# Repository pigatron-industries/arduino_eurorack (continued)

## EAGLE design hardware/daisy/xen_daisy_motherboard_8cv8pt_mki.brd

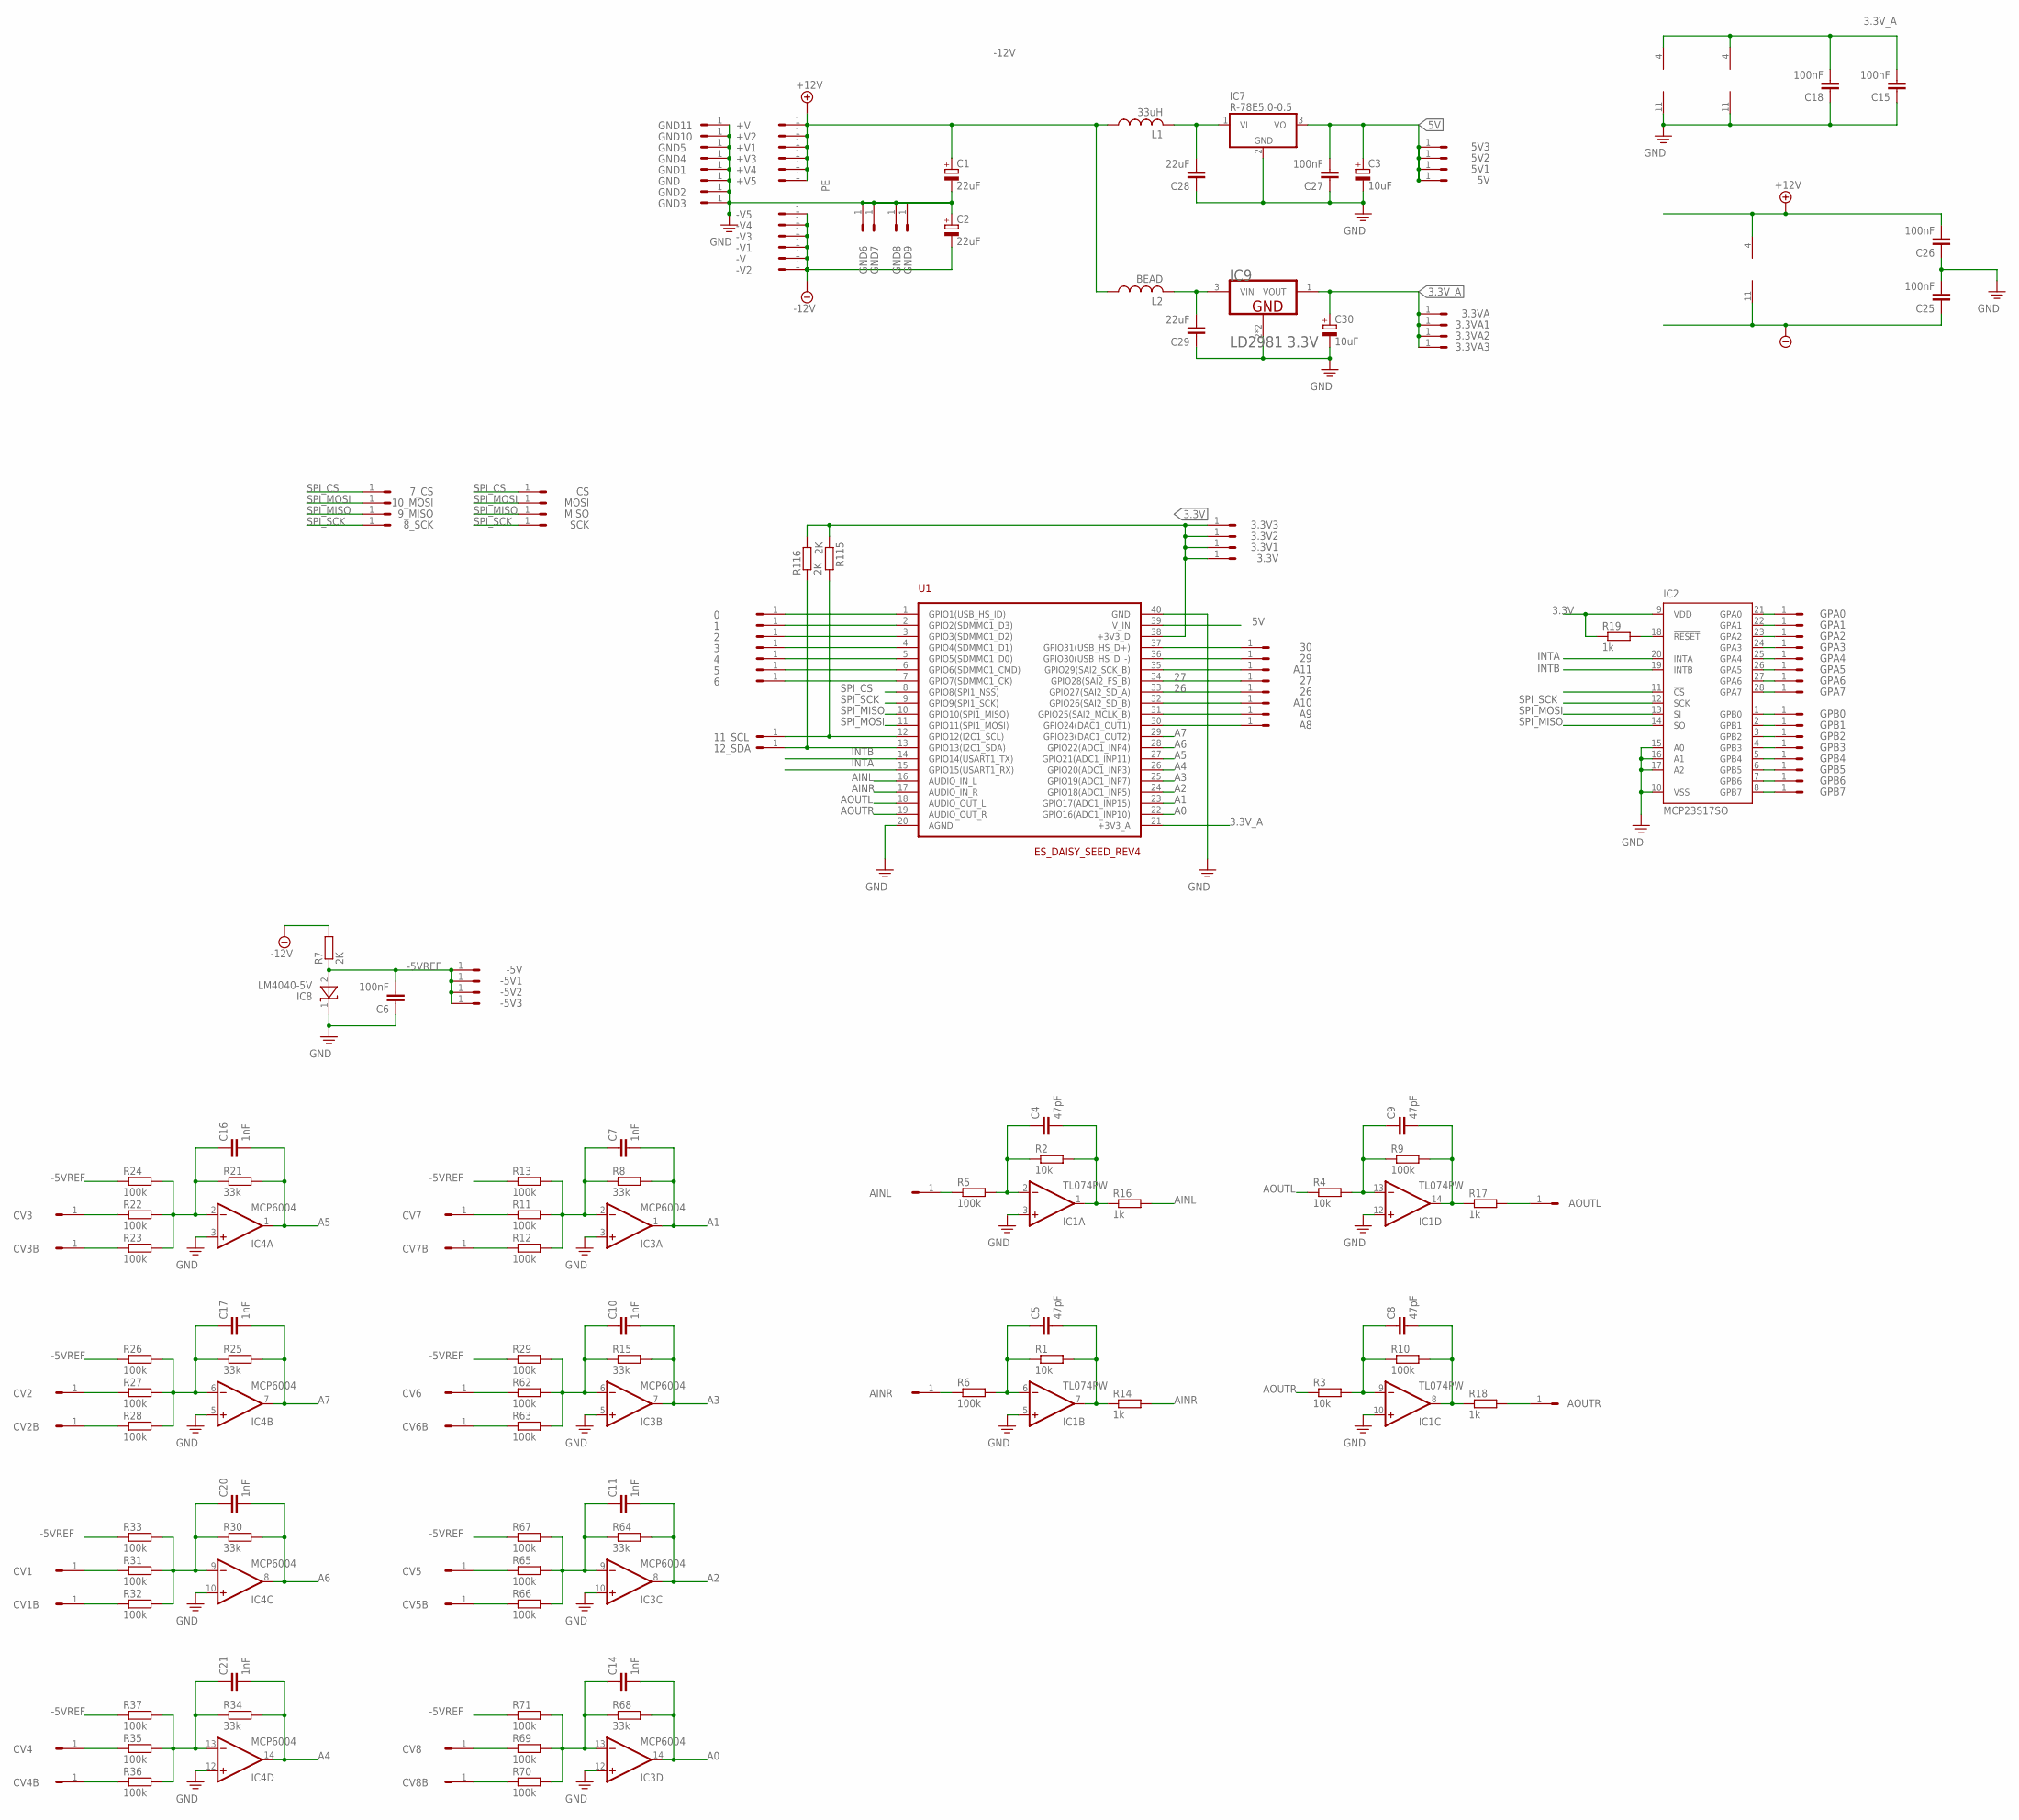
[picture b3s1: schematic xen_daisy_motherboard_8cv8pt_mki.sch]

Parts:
0, 1, 2, 3, 3.3V, 3.3V1, 3.3V2, 3.3V3, 3.3VA, 3.3VA1, 3.3VA2, 3.3VA3, 4, 5, 5V, 5V1, 5V2, 5V3, 6, 7_CS, 8_SCK, 9_MISO, 10_MOSI, 11_SCL, 12_SDA, 26, 27, 29, 30: HEADER/MALE/01
+V, +V1, +V2, +V3, +V4, +V5: HEADER/MALE/01
-5V, -5V1, -5V2, -5V3: HEADER/MALE/01
-V, -V1, -V2, -V3, -V4, -V5: HEADER/MALE/01
A8, A9, A10, A11: HEADER/MALE/01
AINL: HEADER/MALE/01
AINR: HEADER/MALE/01
AOUTL: HEADER/MALE/01
AOUTR: HEADER/MALE/01
C1, C2: 22uF; SV-C
C3, C30: 10uF; SV-B
C4, C5, C8, C9: 47pF; C0603
C6, C15, C18, C25, C26, C27: 100nF; C0603
C7, C10, C11, C14, C16, C17, C20, C21: 1nF; C0603
C28, C29: 22uF; C0805
CS: HEADER/MALE/01
CV1, CV1B, CV2, CV2B, CV3, CV3B, CV4, CV4B, CV5, CV5B, CV6, CV6B, CV7, CV7B, CV8, CV8B: HEADER/MALE/01
GND, GND1, GND2, GND3, GND4, GND5, GND6, GND7, GND8, GND9, GND10, GND11: HEADER/MALE/01
GPA0, GPA1, GPA2, GPA3, GPA4, GPA5, GPA6, GPA7: HEADER/MALE/01
GPB0, GPB1, GPB2, GPB3, GPB4, GPB5, GPB6, GPB7: HEADER/MALE/01
IC1: TL074PW; TSSOP14
IC2: MCP23S17SO; SO28W
IC3, IC4: MCP6004; TSSOP14
IC7: R-78E5.0-0.5; WE78
IC8: LM4040-5V; SOT-23
IC9: LD2981 3.3V; LD2981-SOT89
L1: 33uH; L2012C
L2: BEAD; R0603
MISO: HEADER/MALE/01
MOSI: HEADER/MALE/01
R1, R2, R3, R4: 10k; R0603
R5, R6, R9, R10, R11, R12, R13, R22, R23, R24, R26, R27, R28, R29, R31, R32, R33, R35, R36, R37, R62, R63, R65, R66, R67, R69, R70, R71: 100k; R0603
R7, R115, R116: 2K; R0603
R8, R15, R21, R25, R30, R34, R64, R68: 33k; R0603
R14, R16, R17, R18, R19: 1k; R0603
SCK: HEADER/MALE/01
U1: ES_DAISY_SEED_REV4; ES_DAISY_SEED

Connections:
3.3V: 3.3V.1, 3.3V1.1, 3.3V2.1, 3.3V3.1, IC2.9 (VDD), R19.1, R115.1, R116.2, U1.38 (+3V3_D)
3.3V_A: 3.3VA.1, 3.3VA1.1, 3.3VA2.1, 3.3VA3.1, C15.2, C18.2, C30.+, IC3.4 (V+), IC4.4 (V+), IC9.1 (VOUT), U1.21 (+3V3_A)
5V: 5V.1, 5V1.1, 5V2.1, 5V3.1, C3.+, C27.2, IC7.3 (VO), U1.39 (V_IN)
26: 26.1, U1.33 (GPIO27(SAI2_SD_A))
27: 27.1, U1.34 (GPIO28(SAI2_FS_B))
+12V: +V.1, +V1.1, +V2.1, +V3.1, +V4.1, +V5.1, C1.+, C26.2, IC1.4 (V+), L1.1, L2.1
-5VREF: -5V.1, -5V1.1, -5V2.1, -5V3.1, C6.2, IC8.2 (A), R7.1, R13.1, R24.1, R26.1, R29.1, R33.1, R37.1, R67.1, R71.1
-12V: -V.1, -V1.1, -V2.1, -V3.1, -V4.1, -V5.1, C2.-, C25.1, IC1.11 (V-), R7.2
A0: C14.2, IC3.14 (OUT), R68.2, U1.22 (GPIO16(ADC1_INP10))
A1: C7.2, IC3.1 (OUT), R8.2, U1.23 (GPIO17(ADC1_INP15))
A2: C11.2, IC3.8 (OUT), R64.2, U1.24 (GPIO18(ADC1_INP5))
A3: C10.2, IC3.7 (OUT), R15.2, U1.25 (GPIO19(ADC1_INP7))
A4: C21.2, IC4.14 (OUT), R34.2, U1.26 (GPIO20(ADC1_INP3))
A5: C16.2, IC4.1 (OUT), R21.2, U1.27 (GPIO21(ADC1_INP11))
A6: C20.2, IC4.8 (OUT), R30.2, U1.28 (GPIO22(ADC1_INP4))
A7: C17.2, IC4.7 (OUT), R25.2, U1.29 (GPIO23(DAC1_OUT2))
AINL: R16.2, U1.16 (AUDIO_IN_L)
AINR: R14.2, U1.17 (AUDIO_IN_R)
AOUTL: R4.1, U1.18 (AUDIO_OUT_L)
AOUTR: R3.1, U1.19 (AUDIO_OUT_R)
INTA: IC2.20 (INTA), U1.15 (GPIO15(USART1_RX))
INTB: IC2.19 (INTB), U1.14 (GPIO14(USART1_TX))
unnamed: CV2.1, R27.1
unnamed: A8.1, U1.30 (GPIO24(DAC1_OUT1))
unnamed: A9.1, U1.31 (GPIO25(SAI2_MCLK_B))
unnamed: A10.1, U1.32 (GPIO26(SAI2_SD_B))
unnamed: A11.1, U1.35 (GPIO29(SAI2_SCK_B))
unnamed: C5.1, IC1.6 (-IN), R1.1, R6.2
unnamed: C4.1, IC1.2 (-IN), R2.1, R5.2
unnamed: C7.1, IC3.2 (-IN), R8.1, R11.2, R12.2, R13.2
unnamed: C4.2, IC1.1 (OUT), R2.2, R16.1
unnamed: C5.2, IC1.7 (OUT), R1.2, R14.1
unnamed: AOUTL.1, R17.2
unnamed: AOUTR.1, R18.2
unnamed: CV7B.1, R12.1
unnamed: CV7.1, R11.1
unnamed: C9.1, IC1.13 (-IN), R4.2, R9.1
unnamed: C10.1, IC3.6 (-IN), R15.1, R29.2, R62.2, R63.2
unnamed: C8.1, IC1.9 (-IN), R3.2, R10.1
unnamed: CV6.1, R62.1
unnamed: CV6B.1, R63.1
unnamed: AINL.1, R5.1
unnamed: C8.2, IC1.8 (OUT), R10.2, R18.1
unnamed: CV3.1, R22.1
unnamed: C9.2, IC1.14 (OUT), R9.2, R17.1
unnamed: C16.1, IC4.2 (-IN), R21.1, R22.2, R23.2, R24.2
unnamed: AINR.1, R6.1
unnamed: CV2B.1, R28.1
unnamed: CV3B.1, R23.1
unnamed: 29.1, U1.36 (GPIO30(USB_HS_D_-))
unnamed: C17.1, IC4.6 (-IN), R25.1, R26.2, R27.2, R28.2
unnamed: C21.1, IC4.13 (-IN), R34.1, R35.2, R36.2, R37.2
unnamed: CV4.1, R35.1
unnamed: CV4B.1, R36.1
unnamed: 30.1, U1.37 (GPIO31(USB_HS_D+))
unnamed: CV1B.1, R32.1
unnamed: CV1.1, R31.1
unnamed: C20.1, IC4.9 (-IN), R30.1, R31.2, R32.2, R33.2
unnamed: 0.1, U1.1 (GPIO1(USB_HS_ID))
unnamed: 1.1, U1.2 (GPIO2(SDMMC1_D3))
unnamed: 2.1, U1.3 (GPIO3(SDMMC1_D2))
unnamed: 3.1, U1.4 (GPIO4(SDMMC1_D1))
unnamed: 11_SCL.1, R115.2, U1.12 (GPIO12(I2C1_SCL))
unnamed: 4.1, U1.5 (GPIO5(SDMMC1_D0))
unnamed: 5.1, U1.6 (GPIO6(SDMMC1_CMD))
unnamed: 6.1, U1.7 (GPIO7(SDMMC1_CK))
unnamed: IC2.18 (!RESET), R19.2
unnamed: C28.2, IC7.1 (VI), L1.2
unnamed: 12_SDA.1, R116.1, U1.13 (GPIO13(I2C1_SDA))
unnamed: GPB7.1, IC2.8 (GPB7)
unnamed: GPB6.1, IC2.7 (GPB6)
unnamed: GPB5.1, IC2.6 (GPB5)
unnamed: C14.1, IC3.13 (-IN), R68.1, R69.2, R70.2, R71.2
unnamed: GPB4.1, IC2.5 (GPB4)
unnamed: GPB3.1, IC2.4 (GPB3)
unnamed: CV8.1, R69.1
unnamed: GPB2.1, IC2.3 (GPB2)
unnamed: GPB1.1, IC2.2 (GPB1)
unnamed: GPB0.1, IC2.1 (GPB0)
unnamed: GPA7.1, IC2.28 (GPA7)
unnamed: GPA6.1, IC2.27 (GPA6)
unnamed: GPA5.1, IC2.26 (GPA5)
unnamed: GPA4.1, IC2.25 (GPA4)
unnamed: CV8B.1, R70.1
unnamed: CV5B.1, R66.1
unnamed: CV5.1, R65.1
unnamed: C11.1, IC3.9 (-IN), R64.1, R65.2, R66.2, R67.2
unnamed: C29.2, IC9.3 (VIN), L2.2
unnamed: GPA3.1, IC2.24 (GPA3)
unnamed: GPA2.1, IC2.23 (GPA2)
unnamed: GPA1.1, IC2.22 (GPA1)
unnamed: GPA0.1, IC2.21 (GPA0)
PE: C1.-, C2.+, C3.-, C6.1, C15.1, C18.1, C25.2, C26.1, C27.1, C28.1, C29.1, C30.-, GND.1, GND1.1, GND2.1, GND3.1, GND4.1, GND5.1, GND6.1, GND7.1, GND8.1, GND9.1, GND10.1, GND11.1, IC1.3 (+IN), IC1.5 (+IN), IC1.10 (+IN), IC1.12 (+IN), IC2.10 (VSS), IC2.15 (A0), IC2.16 (A1), IC2.17 (A2), IC3.3 (+IN), IC3.5 (+IN), IC3.10 (+IN), IC3.11 (V-), IC3.12 (+IN), IC4.3 (+IN), IC4.5 (+IN), IC4.10 (+IN), IC4.11 (V-), IC4.12 (+IN), IC7.2 (GND), IC8.1 (C), IC9.2 (GND), IC9.2-2 (GND), U1.20 (AGND), U1.40 (GND)
SPI_CS: 7_CS.1, CS.1, U1.8 (GPIO8(SPI1_NSS))
SPI_MISO: 9_MISO.1, IC2.14 (SO), MISO.1, U1.10 (GPIO10(SPI1_MISO))
SPI_MOSI: 10_MOSI.1, IC2.13 (SI), MOSI.1, U1.11 (GPIO11(SPI1_MOSI))
SPI_SCK: 8_SCK.1, IC2.12 (SCK), SCK.1, U1.9 (GPIO9(SPI1_SCK))

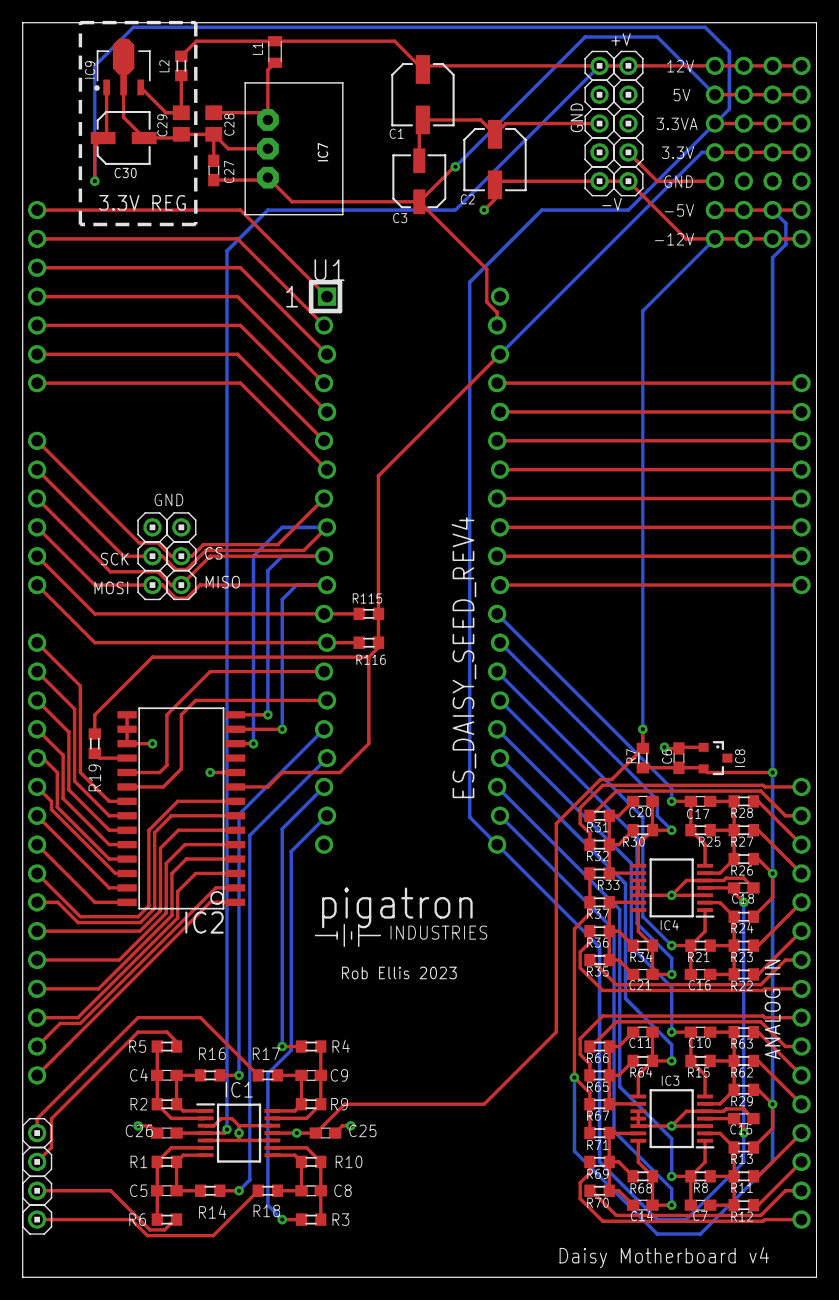
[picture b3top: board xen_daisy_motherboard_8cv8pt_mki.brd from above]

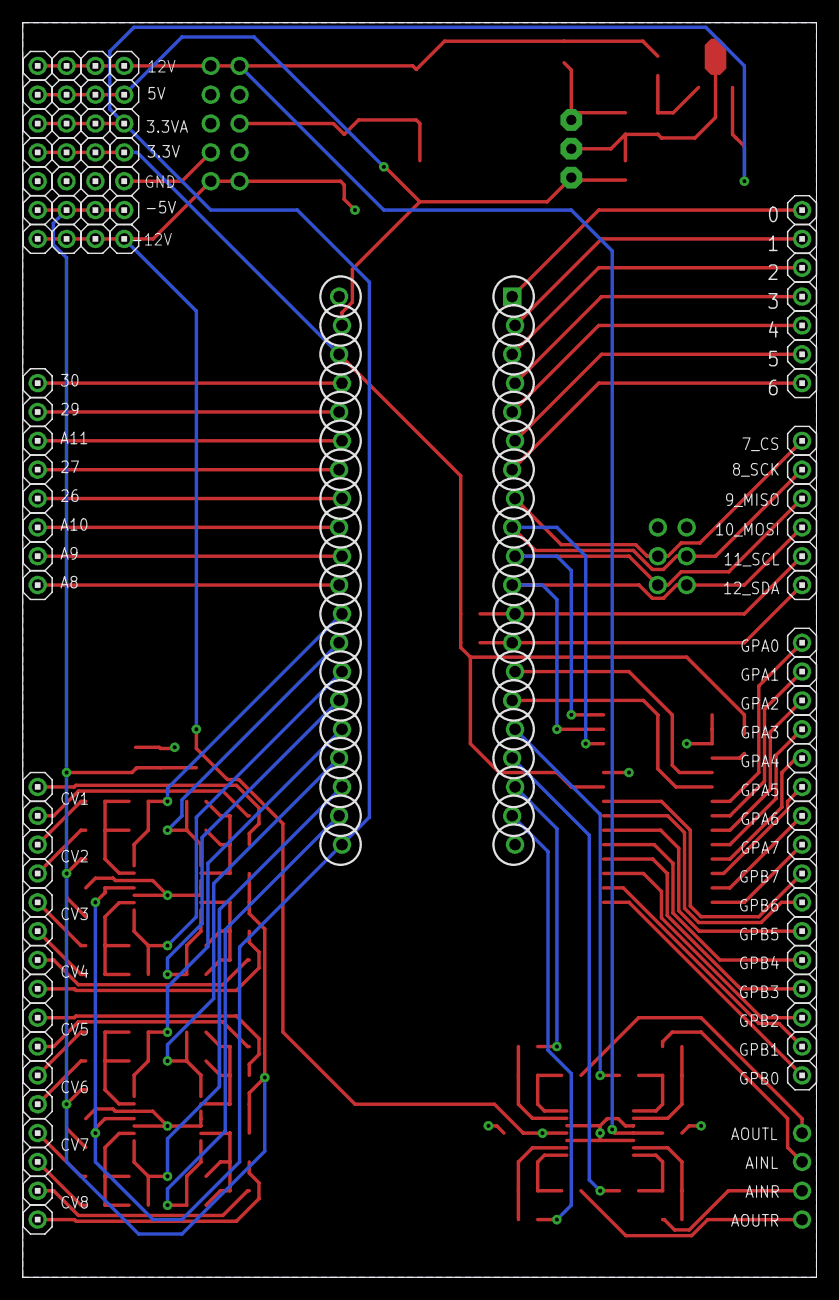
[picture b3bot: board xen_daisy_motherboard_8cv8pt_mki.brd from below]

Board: 2 copper layers, 69.9 x 110.5 mm, 184 parts (81 on the bottom side), 97 nets.

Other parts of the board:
U$1: PIGATRON-LOGO

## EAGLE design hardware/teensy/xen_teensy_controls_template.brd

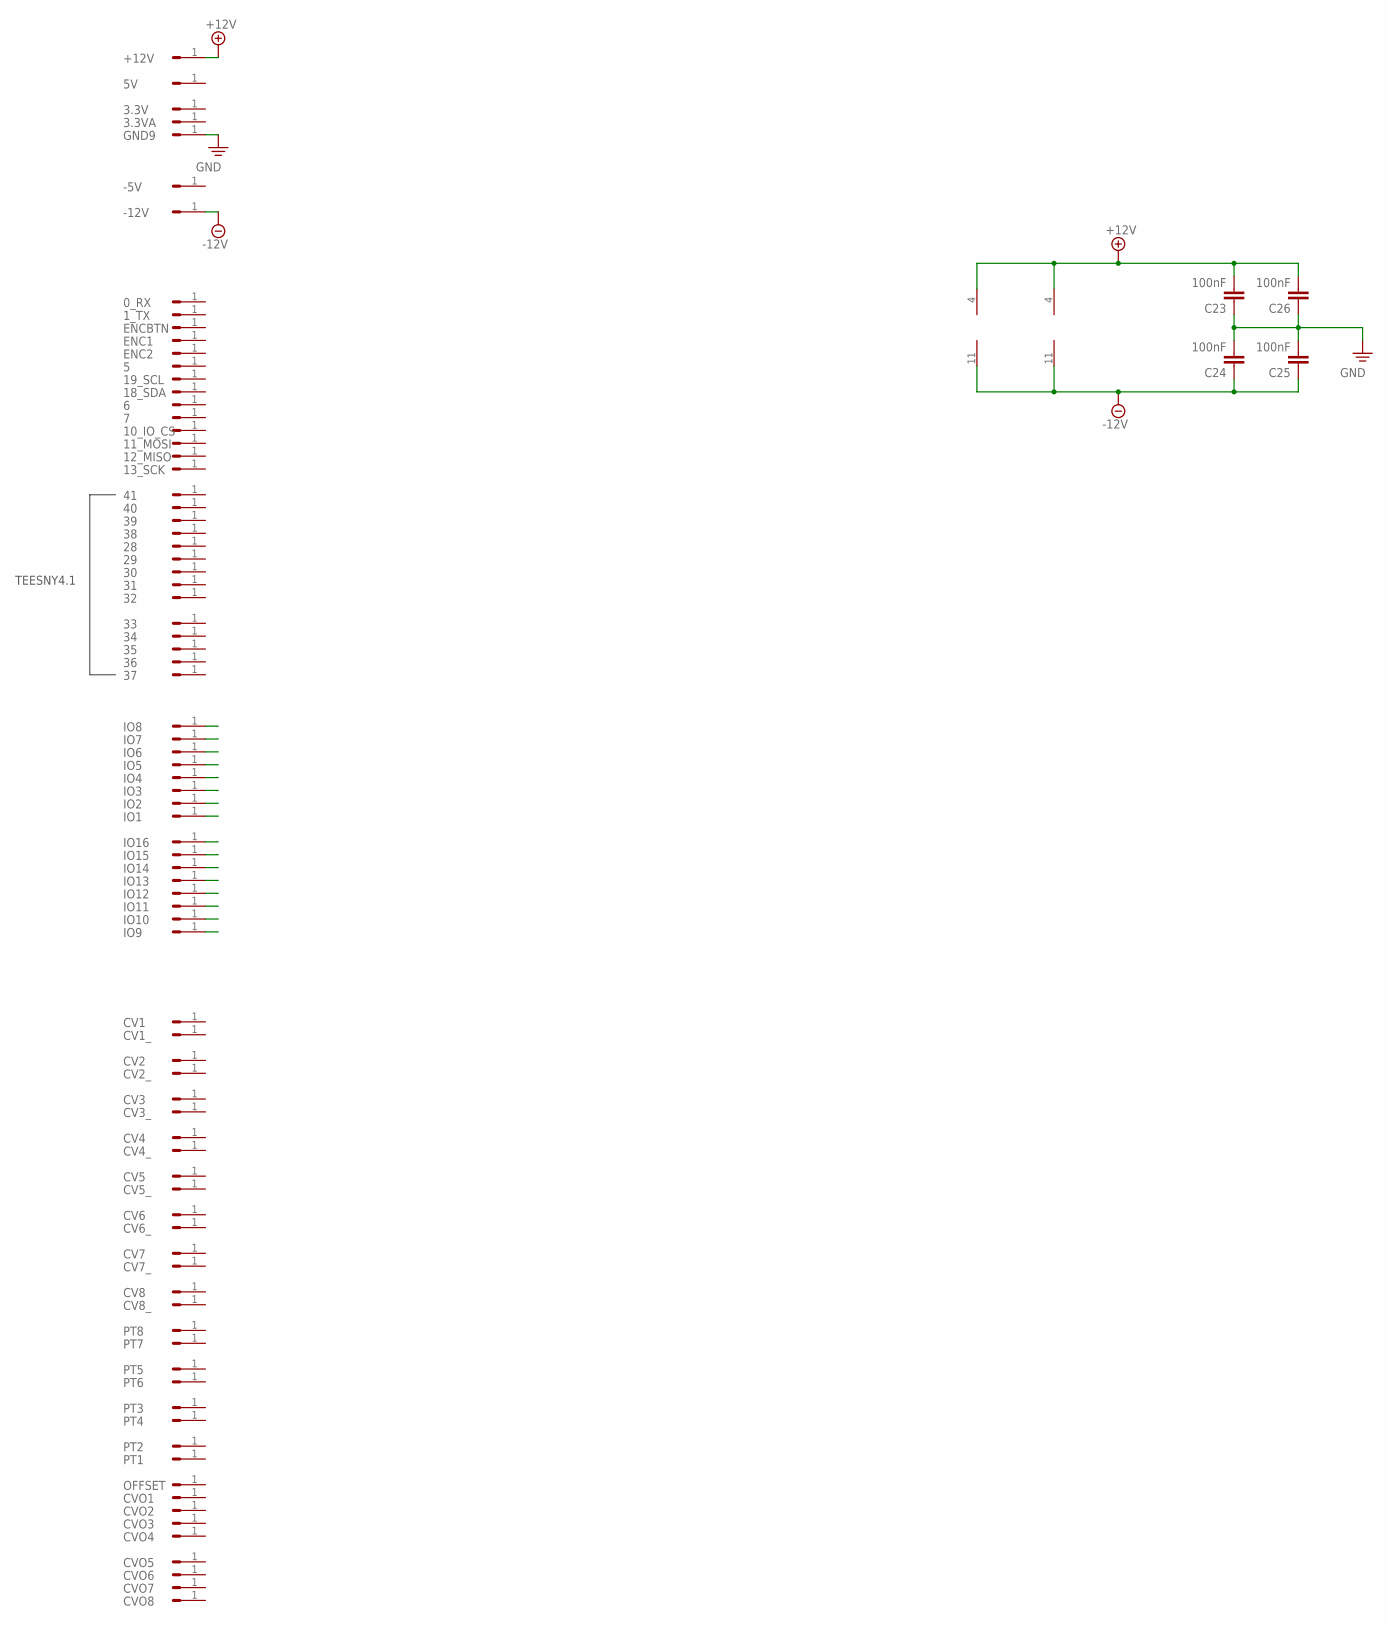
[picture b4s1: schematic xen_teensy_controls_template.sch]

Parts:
0_RX, 1_TX, 3.3V, 3.3VA, 5, 5V, 6, 7, 10_IO_CS, 11_MOSI, 12_MISO, 13_SCK, 18_SDA, 19_SCL, 28, 29, 30, 31, 32, 33, 34, 35, 36, 37, 38, 39, 40, 41: HEADER/MALE/01
+12V: HEADER/MALE/01
-5V, -12V: HEADER/MALE/01
C23, C24, C25, C26: 100nF; C0603
CV1, CV1_, CV2, CV2_, CV3, CV3_, CV4, CV4_, CV5, CV5_, CV6, CV6_, CV7, CV7_, CV8, CV8_: HEADER/MALE/01
CVO1, CVO2, CVO3, CVO4, CVO5, CVO6, CVO7, CVO8: HEADER/MALE/01
ENC1, ENC2: HEADER/MALE/01
ENCBTN: HEADER/MALE/01
GND9: HEADER/MALE/01
IC1, IC5: TL074D; SO14
IO1, IO2, IO3, IO4, IO5, IO6, IO7, IO8, IO9, IO10, IO11, IO12, IO13, IO14, IO15, IO16: HEADER/MALE/01
OFFSET: HEADER/MALE/01
PT1, PT2, PT3, PT4, PT5, PT6, PT7, PT8: HEADER/MALE/01

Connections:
+12V: +12V.1, C23.2, C26.2, IC1.4 (V+), IC5.4 (V+)
-12V: -12V.1, C24.1, C25.1, IC1.11 (V-), IC5.11 (V-)
PE: C23.1, C24.2, C25.2, C26.1, GND9.1

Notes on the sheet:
TEESNY4.1

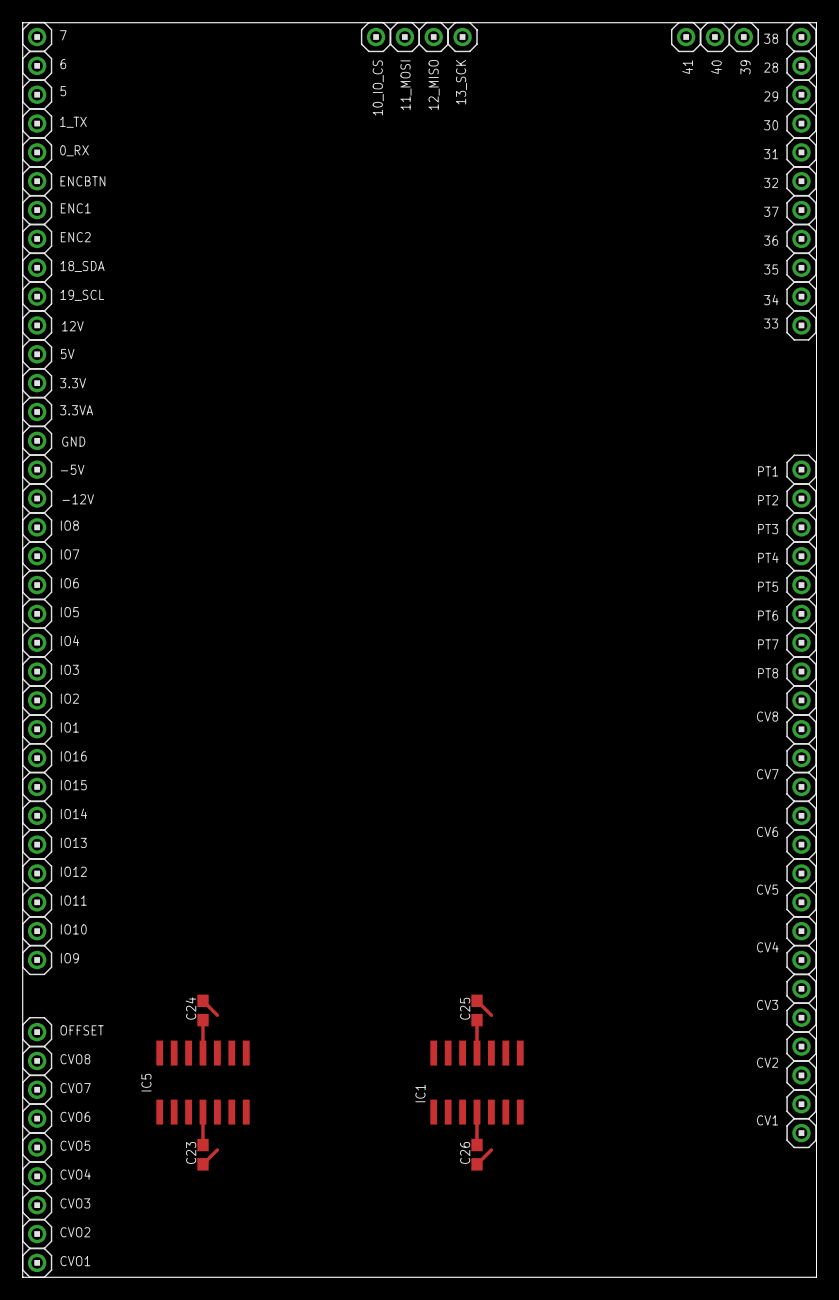
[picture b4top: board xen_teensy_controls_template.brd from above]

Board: 2 copper layers, 69.9 x 110.5 mm, 91 parts (0 on the bottom side), 3 nets.

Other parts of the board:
U$1: PIGATRON-LOGO

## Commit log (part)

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2021-09-04 Added set range methods
2021-09-04 Added compile tests and fixed issues
2021-09-04 inlined methods
2021-09-04 use references
2021-09-04 Set voltage range of max11300 pins
2021-09-04 default to NativeDevice
2021-09-04 add pullup pin type
2021-09-04 automatically set pin type
2021-09-04 auto set pin types
2021-09-04 macros for defining native io
2021-09-04 removed debounce.begin call becasue it crashes
2021-09-04 implement deferred output for max11300
2021-09-04 Fix compile error
2021-09-12 V0.2 (#2)
    * v0.2 rewrite
    * Fix hc595 error
    * Used virtual inheritance
    * Added binary read method
    * Added set range methods
    * Added compile tests and fixed issues
2021-09-12 Add getSize
2021-09-27 Add pin enable method
2021-09-28 Added IS32FL3738 led driver as analog output device
2021-10-02 Fix for range scale not working when to values are inverted
2021-10-02 DAC8164 device driver
2021-10-02 Added set duration for trigger
2021-10-02 getPhase method
2021-10-03 Add filter, move oscillator
2021-10-03 include math.h
2021-10-10 Array wrapper
2021-10-10 Array operator
2021-10-12 Sample Buffer
2021-10-12 Set sampleRate
2021-10-16 Added MemPool class and SamplePlayer
2021-10-17 Add teensy motherboard pcb
2021-10-30 decalre overloaded new operator to make this compile on teensy for now
2021-10-30 Rewritten envelope to use segments instead of points
2021-10-30 Added sustain to envelope
2021-10-30 Only return true if gate has changed
2021-11-14 const [] operator
2021-11-15 Moved hardware
2021-11-18 profiler
2021-11-18 seperate print from end
2021-11-18 fix method name
2021-11-21 Add speed to SlewLimiter constructor
2021-12-05 Correct method name
2021-12-06 Add DelayLine
2021-12-06 Made MemPool a template
2021-12-06 don't use new to allocate memory
2021-12-06 Fixed delay line position calcualtion
2021-12-06 set total delay
2021-12-20 Use template type for pointer type
2021-12-20 Added const
2021-12-20 Set max clock speed for i2c
2021-12-28 Adde AbstractMainController and Config
2021-12-28 Add clock and clock divider
2021-12-29 Fixed bugs in HC595Device
2021-12-29 Removed MultiplexGateOutput, use HC595Device instead
2021-12-29 Remove MultiplexGateOutput
2021-12-29 Add Timer include
2021-12-29 Added Wire.h
2021-12-29 made interface he same as GateOutput
2021-12-29 initialise in constructor
2022-01-02 Inverted gate input
2022-01-15 Reduce default trigger voltage to 2v
2022-01-28 Added waveshapes and WaveOscillator
2022-01-28 added waveshapes to include
2022-01-28 Made controllerInit virtual
2022-01-28 option to invert gate input
2022-01-29 Added setPhase method
2022-01-29 Allow oscillator to have negative frequency
2022-01-29 Base class for oscillators
2022-01-29 Fix local variable bug
2022-01-29 Set length of each segment to equal 1
2022-01-29 Added AsymmetricalTriangle
2022-01-29 calculate gradient and total length when changing line length
2022-01-29 Replace envelope with waves shape based envelope
2022-01-29 Don't do anything if gate value didn't change
2022-01-30 Replaced WaveList with WaveSelector
2022-01-30 Add ObjectSelector to include
2022-01-30 Add array operator to ObjectSelector
2022-01-30 Fix error
2022-01-31 Add cycle methods
2022-01-31 getSize method
2022-02-01 Renamed ObjectSelector
2022-02-01 Use ObjectSelector instead of ControllerList
2022-02-01 Use TypeSelector to select controllers
2022-02-01 Fixed bug setting index to 0
2022-02-02 Changed constants due to clashes with arduino framework
2022-02-04 Add AbstrctController
2022-02-04 Add AbstractController
2022-02-04 object to manage an encoder with button together
2022-02-04 use combined encoder and button in main controller
2022-02-04 Adding eurorack namespace
2022-02-04 Added eurorack namespace
2022-02-04 Removed old oscillator class
2022-02-04 Added bandlimited waveforms
2022-02-04 method to enable polyblep
2022-02-04 Set oscillator amplitude
2022-02-06 WaveTable
2022-02-06 WaaveTable
2022-02-06 Add getTableFrequency
2022-02-06 Added isInited method
2022-02-06 Add temp buffer to WaveTable
2022-02-06 Added WaveTable super class
2022-02-06 Added WaveTableFactory
2022-02-06 Added namespace
2022-02-07 Aadded missing incrementPhase()
2022-02-11 Add missing return statement
2022-02-11 WaveSelector and TypeSelector constructors
2022-02-11 WaveInterpolator
2022-02-12 Updated hardware
2022-02-12 Phase distortion oscillator
2022-02-13 Added basic 2 line distortion function
2022-02-15 Added maxPhase variable
2022-02-15 Update docs
2022-02-19 Return last value if after end of sequence
2022-02-19 Made some methods protected
2022-02-24 Split up getEncoderEvent to make it easier to override
2022-02-25 AnalogGateOutput
2022-02-26 setLength method
2022-02-27 Set theme jekyll-theme-tactile
2022-02-27 index.md
2022-02-27 formatting
2022-02-27 Documentation links
2022-02-27 -5v reference circuit
2022-02-27 added style
2022-02-27 doc theme
2022-02-27 override layout
2022-02-27 layout
2022-02-27 Link to documentation
2022-02-27 doc style
2022-02-27 Add logo
2022-02-27 move links to sidebar
2022-02-27 link to homepage
2022-02-27 Add links in sidebar
2022-02-27 links to pages
2022-02-27 fix url
2022-02-27 Ordered pages
2022-02-27 Highlight acrive page
2022-02-27 fix navigation
2022-02-28 Header font
2022-02-28 use baseUrl
2022-02-28 change title
2022-02-28 fix baseUrl
2022-02-28 baseurl
2022-02-28 try to fix baseurl
2022-02-28 add slash
2022-03-03 use css from main site
2022-03-03 use style from main site
2022-03-03 layout change
2022-03-04 no title for main page
2022-03-05 use common layout
2022-03-05 basic usage
2022-03-05 features and status
2022-03-05 nested bullets
2022-03-05 split tested and untested list
2022-03-05 moved usage to new page
2022-03-06 typo
2022-03-10 smooth step function
2022-03-10 Constructor
2022-03-10 calc coefficients in constructor
2022-03-11 Update TriggerInput to use device pins
2022-03-11 remove old TriggerInput
2022-03-11 remove old TrigggerInput
2022-03-11 Changed Object selector to Array selector
2022-03-11 Fix issue
2022-03-12 Moved interpolator logic to base class
2022-03-12 Change to private inheritance
2022-03-12 Add array operator
2022-03-12 2D and 3D Interpolators
2022-03-12 docs
2022-03-12 renamed
2022-03-12 title
2022-03-12 chnaged title levels
2022-03-12 images
2022-03-13 interpolatot docs
2022-03-13 WaveInterpolator2D
2022-03-14 Set pin types in init function
2022-03-14 Add getSize method
2022-03-14 Moved function to .h file
2022-03-15 enable interrupts on init
2022-03-16 Enable deferred output
2022-03-16 Set interrupt pin to input
2022-03-16 Receive method to read all input pins
2022-03-16 added deferred input
2022-03-17 check for digital_input_pullup
2022-03-17 deferred initialization
2022-03-18 don't read pin value in constructor
2022-03-18 Removed digital read from constructor
2022-03-18 EnumInput
2022-03-18 Enum input fix
2022-03-18 EnumInput fix
2022-03-19 teensy motherboard docs
2022-03-19 hardware docs
2022-03-19 add labels to image
2022-03-19 made image bigger
2022-03-19 add header
2022-03-19 numbering
2022-03-19 pin label
2022-03-19 labels
2022-03-19 rotate labels
2022-03-20 crop image
2022-03-20 label power
2022-03-20 pin descriptions
2022-03-20 Teensy connections
2022-03-20 resize
2022-03-21 Check index is within range
2022-03-21 don't deferr init on native device
2022-03-21 Add SDB pin
2022-03-21 Split out saveMode function
2022-03-21 remove selected reference as it was always referencing first item
2022-03-21 AnalogInputSumPin
2022-03-25 Changed templates to allow other analog pin types to be passed in
2022-03-25 add constant for default mid value
2022-03-25 change to unsigned
2022-03-27 Increase default trigger length
2022-03-27 Add pullup option to DigitalInputPin
2022-03-31 Added state varialbe to envelope
2022-04-01 Prevent envelope attack and decay jumping if gate changes when not fully finished phase
2022-04-02 renamed AbstractInput to AbstractAnalogInput
2022-04-02 Add invert parameter to DigitalInput macro
2022-04-02 Add isTriggeredOff function
2022-04-02 update AnalogGateInput doc
2022-04-02 inherit directly from AbstractAnalogInput
2022-04-02 Add debounce to analog gate input
2022-04-10 Allow to change base value
2022-04-12 Reduce noise on analog inputs by averaging and discarding outliers
2022-04-12 PowerFunction
2022-04-12 Constructor parameters
2022-04-12 AnalogInputFilter
2022-04-13 Init for NativeDevice
2022-04-13 Use ADC library for teensy
2022-04-13 Swap custom noise filtering with hardware averaging
2022-04-13 Remove custom NoiseFilter
2022-04-13 configure all adc modules
2022-04-14 Add stabilise threshold back in
2022-04-15 get state and frequency, min wait time for external clock
2022-04-16 replace EnumInput with IntegerInput
2022-04-17 use 0.49 to prevent round outside of range
2022-04-18 update template
2022-04-18 Don't let long hold events prevent rotation event from triggering.
2022-04-28 Array initialiser
2022-04-29 changed traces
2022-05-01 Change dependencies
2022-05-01 contains method
2022-05-22 Added handy operators
2022-05-23 bug fix
2022-06-08 Add ArrayPtr to allow passing arrays without knowing size at compile time
2022-06-11 Set output range
2022-06-11 Add sd card reader
2022-06-11 sd header
2022-06-11 initialise as sdio when not setting csPin
2022-06-11 common begin function
2022-06-11 add BufferFileReader to header
2022-06-11 add const
2022-06-11 simple wildcard match function
2022-06-12 moved mempool added linked list
2022-06-12 add object
2022-06-18 getObjects
2022-06-18 Allow encoder control schem to be redefined
2022-06-18 Cyle value methods
2022-06-18 extra constructors
2022-06-18 option to initialise on mode select
2022-07-02 add SdFat
2022-07-02 getObjects method
2022-07-02 Store reciprocal of length to make gradient calculation more efficient
2022-07-02 inlined
2022-07-02 set length in constructor
2022-07-09 Add calibrated scale to analog pins
2022-07-09 Add offset and scale methods
2022-07-09 recalculate factor after scale and offset
2022-07-09 load ans save analog pin calibration
2022-07-09 changed scale direction
2022-08-04 Added pin calibration class
2022-08-05 Added error on array overflow
2022-08-12 Allow second encoder
2022-08-13 added clear function and remove memory deletions
2022-08-20 Add graphics layout library
2022-08-21 Horizontal container
2022-08-21 FieldComponent minor updates
2022-09-12 documentation
2022-09-12 Try SPI, fallback to SDIO
2022-09-19 removed calls the sd.end() as it closes the spi bus completely
2022-09-20 getTrigger without resetting
2022-09-20 add save and load method to controller
2022-09-20 moved methods to abstract controller
2022-12-03 importing SPI.h avoids compile errors in projects that don't import it
2022-12-03 call save method after changing mode
2023-06-18 use unsigned char for file reader buffer
2023-06-20 memmem implementation
2023-07-14 add seperate double and single encoder controllers
2023-07-14 separate controllers for double encoder
2023-07-19 parameterized controller
2023-07-21 remove superclass
2023-08-17 remove item from array
2023-10-22 add selectValue method
2023-10-22 add heldFor duration method
2023-10-22 fix heldFor function
2023-10-29 add getPin function
2023-10-29 add get scale and offset methods
2023-11-11 fix bug with config check
2023-11-27 Allow cycle enums to be cycled and selected
2024-01-20 add init function to Array
2024-01-22 split out external clock and add tests
2024-01-26 add clock divider to external clock
2024-01-26 add test
2024-01-26 add clock multiplier
2024-01-26 if external tick is late wait for it
2024-01-26 add InternalExternalClock to include header
2024-01-26 fix include
2024-01-26 remove inline
2024-01-27 add set items and get method
2024-03-23 include LinkedList
2024-03-23 Remove ObjectManager
2024-03-23 remove mempool from LinkedList constructor, add allocateObject function
2024-03-23 remove mempool
2024-03-25 allocate buffer in generic mempool
2024-03-26 encoder non-interrupt mode
2024-03-26 make saveState virtual
2024-03-27 filter file list by extension
2024-03-28 add abstract classes
2024-03-29 set pullup pins
2024-03-31 mempool fix
2024-04-01 make methods virtual
2024-04-26 correct type
2024-05-19 getGate
2024-06-23 handly methods
2024-07-07 upgradee teensy, remove sdfat library
2024-12-24 add process to sample player
2024-12-24 nuulptr fix
2024-12-25 setLoop
